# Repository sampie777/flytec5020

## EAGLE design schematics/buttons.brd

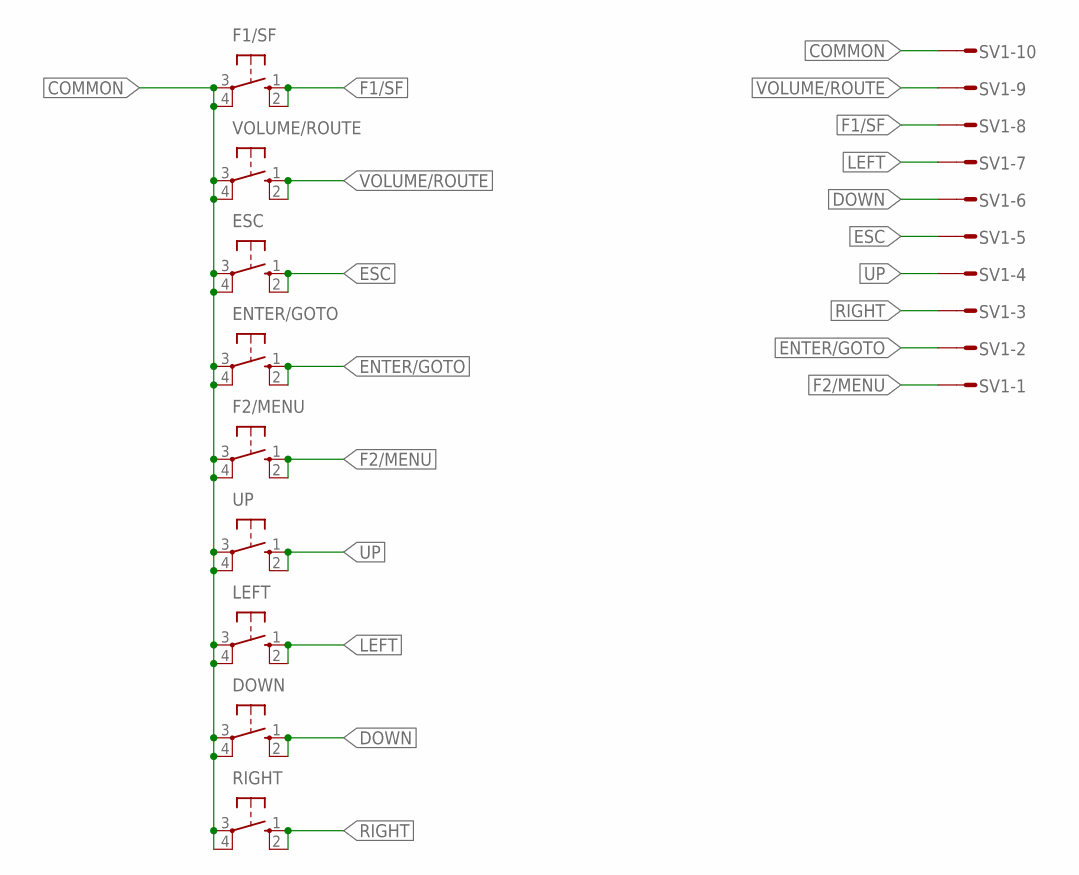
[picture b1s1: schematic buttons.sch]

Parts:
DOWN: 10-XX; B3F-10XX
ENTER/GOTO: 10-XX; B3F-10XX
ESC: 10-XX; B3F-10XX
F1/SF, F2/MENU: 10-XX; B3F-10XX
LEFT: 10-XX; B3F-10XX
RIGHT: 10-XX; B3F-10XX
SV1: S10P
UP: 10-XX; B3F-10XX
VOLUME/ROUTE: 10-XX; B3F-10XX

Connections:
COMMON: DOWN.3, DOWN.4 (P1), ENTER/GOTO.3, ENTER/GOTO.4 (P1), ESC.3, ESC.4 (P1), F1/SF.3, F1/SF.4 (P1), F2/MENU.3, F2/MENU.4 (P1), LEFT.3, LEFT.4 (P1), RIGHT.3, RIGHT.4 (P1), SV1.10, UP.3, UP.4 (P1), VOLUME/ROUTE.3, VOLUME/ROUTE.4 (P1)
DOWN: DOWN.1 (S), DOWN.2 (S1), SV1.6
ENTER/GOTO: ENTER/GOTO.1 (S), ENTER/GOTO.2 (S1), SV1.2
ESC: ESC.1 (S), ESC.2 (S1), SV1.5
F1/SF: F1/SF.1 (S), F1/SF.2 (S1), SV1.8
F2/MENU: F2/MENU.1 (S), F2/MENU.2 (S1), SV1.1
LEFT: LEFT.1 (S), LEFT.2 (S1), SV1.7
RIGHT: RIGHT.1 (S), RIGHT.2 (S1), SV1.3
UP: SV1.4, UP.1 (S), UP.2 (S1)
VOLUME/ROUTE: SV1.9, VOLUME/ROUTE.1 (S), VOLUME/ROUTE.2 (S1)

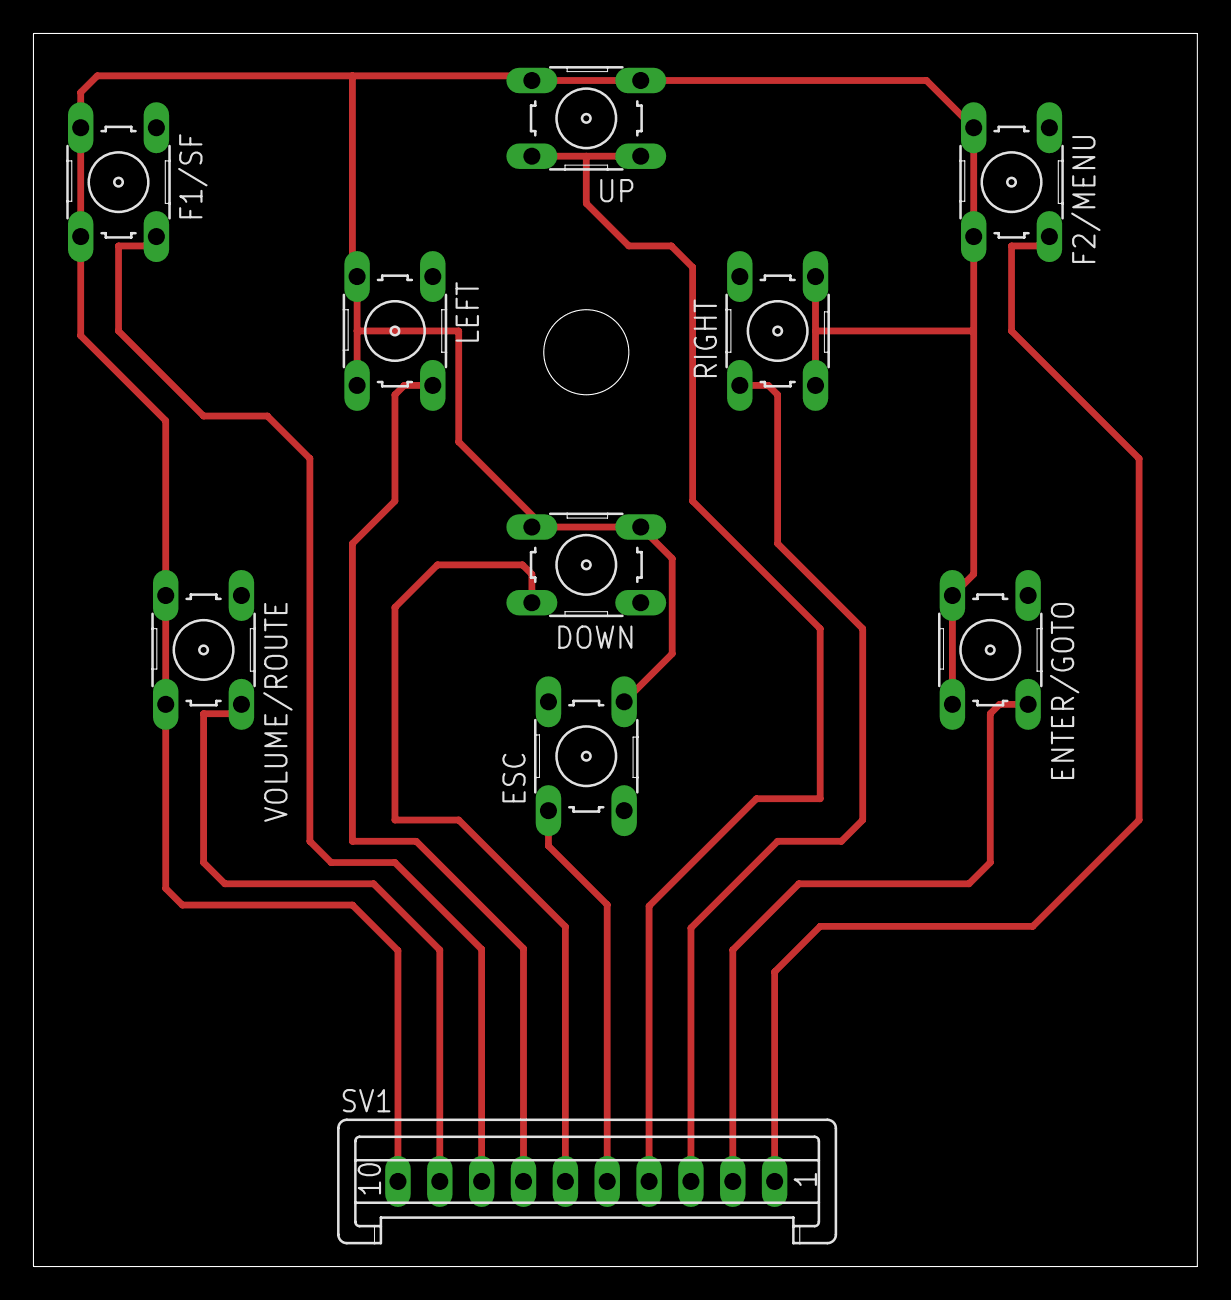
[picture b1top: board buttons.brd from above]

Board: 2 copper layers, 69.5 x 73.7 mm, 10 parts (0 on the bottom side), 10 nets.

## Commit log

2023-11-29 Added schematics for serial connection
2023-11-29 Added schematics and rough PCB for buttons
2023-11-29 Added screenshot for buttons
